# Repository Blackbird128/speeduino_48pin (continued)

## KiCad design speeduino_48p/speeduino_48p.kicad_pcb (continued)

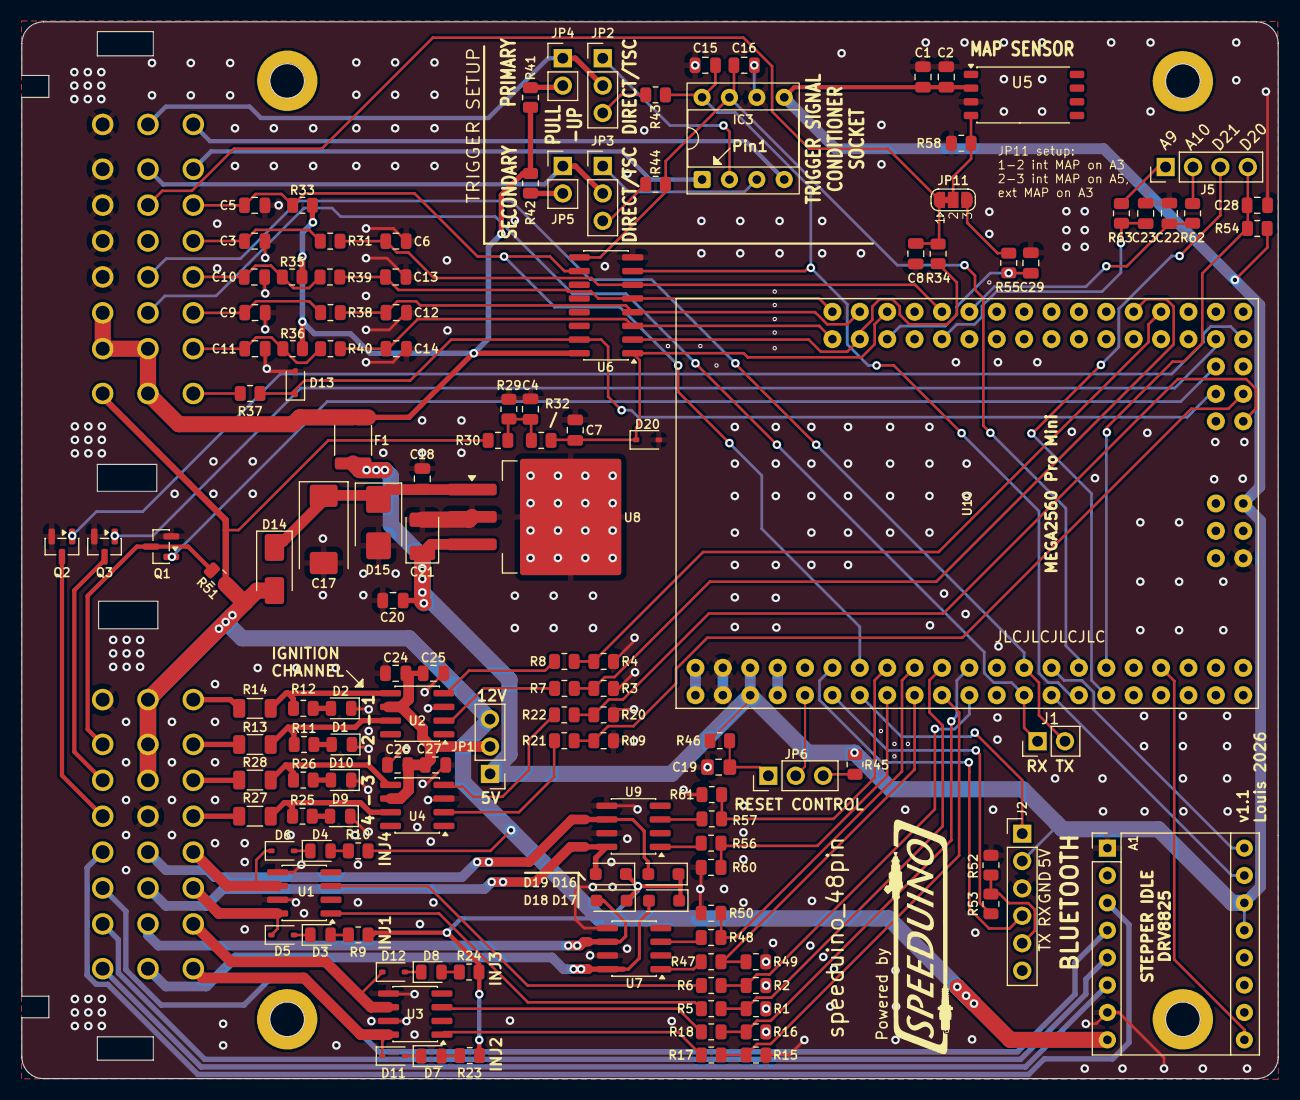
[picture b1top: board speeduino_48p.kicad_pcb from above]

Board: 2 copper layers, 116.5 x 98.0 mm, 143 parts (0 on the bottom side), 118 nets.

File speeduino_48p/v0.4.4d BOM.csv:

Reference; Quantity; Value; Footprint; Manufacturer_Name; Manufacturer_Part_Number; URL; Part #; Voltage; Allied_Number; Description; RS Part Number; RS Price/Stock; TR PN; Tube PN; Spice_Model; Spice_Netlist_Enabled; Spice_Primitive
C1 C15;2;0.01uF;Capacitor_SMD:C_0805_2012Metric;Yageo;CC0805KRX7R9BB103;https://www.digikey.com/product-detail/en/yageo/CC0805KRX7R9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;;;;;;;;;;;
C17;1;10uF;Capacitor_Tantalum_SMD:CP_EIA-7343-31_Kemet-D;Kemet;T491D106K050AT;https://www.digikey.com/product-detail/en/kemet/T491D106K050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;;35v;;;;;;;;;
C19;1;22uF;Capacitor_SMD:C_0805_2012Metric_Pad1.15x1.40mm_HandSolder;Samsung;CL21A226KQCLRNC;https://www.digikey.com.au/product-detail/en/samsung-electro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;;;;;;;;;;;
C21;1;47uF;Capacitor_Tantalum_SMD:CP_EIA-3528-21_Kemet-B;AVX;TAJB476K006RNJ;https://www.digikey.com/product-detail/en/avx-corporation/TA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;;10v;;;;;;;;;
C24 C26 C3 C9 C10 C11 C4 C16 C18 C20 C23 C22 C28;13;0.1uF;Capacitor_SMD:C_0805_2012Metric;Yageo;CC0805KRX7R9BB104;https://www.digikey.com.au/product-detail/en/yageo/CC0805KRX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;;;;;;;;;;;
C25 C27 C2;3;1uF;Capacitor_SMD:C_0805_2012Metric;Yageo;CC0805KKX7R7BB105;https://www.digikey.com/product-detail/en/yageo/CC0805KKX7R7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;;;;;;;;;;;
C6 C12 C13 C14 C7 C5;6;0.22uF;Capacitor_SMD:C_0805_2012Metric;Samsung;CL21B224KOCNNNC;https://www.digikey.com/product-detail/en/samsung-electro-me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;;;;;;;;;;;
C8 C29;2;470pf;Capacitor_SMD:C_0805_2012Metric;Yageo;CC0805KRX7R9BB471;https://www.digikey.com/product-detail/en/yageo/CC0805KRX7R9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;;;;;;;;;;;
D12 D11 D5 D6;4;D;Diode_SMD:D_SOD-323;MCC;1N4448WX-TP;https://www.digikey.com/product-detail/en/micro-commercial-c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;;;;;;;;;;;
D13 D20;2;D_Zener;Diode_SMD:D_SOD-323;On Semi;MM3Z5V1ST1G;https://www.digikey.com/product-detail/en/on-semiconductor/M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;MM3Z5V1ST1G;;;;;;;;;;
D14;1;B130-13-F;Diode_SMD:D_SMA;Diodes Inc;B130-13-F;https://www.digikey.com.au/product-detail/en/diodes-incorpor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;;;;;;;;;;;
D15;1;D_TVS;Diode_SMD:D_SMB;Bournes Inc.;SMBJ40A-Q;https://www.digikey.com.au/product-detail/en/bourns-inc/SMBJ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;;;;;;;;;;;
D19 D16 D17 D18;4;D;Diode_SMD:D_SOD-123F;ONSEMI;S110FA;https://www.digikey.com/en/products/detail/on-semiconductor/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;;;;;;;;;;;
D4 D3 D8 D7 D1 D2 D9 D10;8;LED;LED_SMD:LED_0805_2012Metric;Osram;LH R974-LP-1;https://www.digikey.com/product-detail/en/osram-opto-semicon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;;;;;;;;;;;
F1 F2;2;Polyfuse;Fuse:Fuse_1812_4532Metric;Bel Fuse;0ZCC0050FF2C;https://www.digikey.com.au/product-detail/en/bel-fuse-inc/0Z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;;;;;;;;;;;
IC3;2;Trig Cond Socket;Package_DIP:DIP-8_W7.62mm_Socket;Sullins Connector Solutions;PPTC041LFBN-RC;https://www.digikey.com.au/product-detail/en/sullins-connect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;;;;;;;;;;;
J3;1;Conn_01x02;TerminalBlock_Phoenix:TerminalBlock_Phoenix_PT-1,5-2-5.0-H_1x02_P5.00mm_Horizontal;TE;282836-2;https://www.digikey.com.au/product-detail/en/te-connectivity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;;;;;;;;;;;
J4;1;Conn_02x20_Counter_Clockwise;Connector_IDC:IDC-Header_2x20_P2.54mm_Vertical;CNC Tech;571-5103308-8;https://www.digikey.com.au/products/en?keywords=1175-1614-ND;;;;;;;;;;;
JP1;1;Ignition Voltage;Connector_PinHeader_2.54mm:PinHeader_1x03_P2.54mm_Vertical;Harwin Inc;M20-9990345;https://www.digikey.com.au/products/en?keywords=M20-9990345;;;;;;;;;;;
JP2 JP3;2;VR-HALL;Connector_PinHeader_2.54mm:PinHeader_1x03_P2.54mm_Vertical;Harwin Inc;M20-9990345;https://www.digikey.com.au/products/en?keywords=M20-9990345;;;;;;;;;;;
JP5 JP4;2;PULL-UP;Connector_PinHeader_2.54mm:PinHeader_1x02_P2.54mm_Vertical;Harwin Inc;M20-9990245;https://www.digikey.com.au/products/en?keywords=M20-9990245;;;;;;;;;;;
Q1 Q3 Q2;3;SSM3K357R;Package_TO_SOT_SMD:SOT-23;Toshiba;SSM3K357R;https://www.digikey.com.au/product-detail/en/toshiba-semicon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;;;;;;;;;;;
R1 R2 R15 R16 R3 R4 R19 R20 R50 R49 R61 R60;12;100k;Resistor_SMD:R_0805_2012Metric;Yageo;RC0805FR-07100KL;https://www.digikey.com/product-detail/en/yageo/RC0805FR-071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;;;;;;;;;;;
R10 R9 R24 R23 R11 R12 R25 R26 R33;9;2.4k;Resistor_SMD:R_0805_2012Metric;Yageo;RC0805FR-072K4L;https://www.digikey.com/product-detail/en/yageo/RC0805FR-072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;;;;;;;;;;;
R27 R28 R13 R14;4;10R;Resistor_SMD:R_1206_3216Metric;Yageo;RC1206FR-0710RL;https://www.digikey.com/en/products/detail/yageo/RC1206FR-07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;;;;;;;;;;;
R30;1;3.9k;Resistor_SMD:R_0805_2012Metric;Yageo;RC0805FR-073K9L;https://www.digikey.com/product-detail/en/yageo/RC0805FR-073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;;;;;;;;;;;
R34 R31 R38 R39 R40 R32 R55 R63 R62;9;470R;Resistor_SMD:R_0805_2012Metric;Panasonic;ERJ-6ENF4700V;https://www.digikey.com/product-detail/en/panasonic-electron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;;;;;;;;;;;
R35 R36;2;2.49k;Resistor_SMD:R_0805_2012Metric;Yageo;RT0805BRD072K49L;https://www.digikey.com/product-detail/en/yageo/RT0805BRD072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;;;;;;;;;;;
R43 R44;2;220R;Resistor_SMD:R_0805_2012Metric;Yageo;RC0805FR-07220RL;https://www.digikey.com/product-detail/en/yageo/RC0805FR-072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;;;;;;;;;;;
R45 R51;2;10k;Resistor_SMD:R_0805_2012Metric;Yageo;RC0805JR-0710KL;https://www.digikey.com/product-detail/en/yageo/RC0805JR-071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;;;;;;;;;;;
R46;1;120R;Resistor_SMD:R_0805_2012Metric;Yageo;RC0805FR-07120RL;https://www.digikey.com/product-detail/en/yageo/RC0805FR-071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;;;;;;;;;;;
R5 R6 R17 R18 R7 R8 R21 R22 R29 R37 R41 R42 R47 R48 R56 R57 R53 R54;18;1k;Resistor_SMD:R_0805_2012Metric;Yageo;RC0805FR-071KL;https://www.digikey.com/product-detail/en/yageo/RC0805FR-071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;;;;;;;;;;;
R52;1;2k;Resistor_SMD:R_0805_2012Metric;Yageo;RC0805FR-072KL;https://www.digikey.com/product-detail/en/yageo/RC0805FR-072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;;;;;;;;;;;
S1;1;AYZ0202AGRLC;Misc:AYZ0202AGRLC;C & K COMPONENTS;AYZ0202AGRLC;https://www.digikey.com.au/product-detail/en/c-k/AYZ0202AGRL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;;;70417470;AYZ0202AGRLC (Slide Switches);7931504P;http://uk.rs-online.com/web/p/products/7931504P;;;;;
U1 U3 U7 U9;4;VNLD5090;Package_SO:SOIC-8_3.9x4.9mm_P1.27mm;STMicro;VNLD5090-E;https://www.digikey.com.au/products/en?keywords=VNLD5090-E;;;;;;;;;;;
U2 U4;2;IXDN602;Package_SO:SOIC-8_3.9x4.9mm_P1.27mm;IXYS;IXDN602SIATR;https://www.digikey.com/en/products/detail/ixys-integrated-c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;;;;;;;;;;;
U5;1;MPX4250;Misc:MPX4250;NXP;MPX4250AP;https://www.digikey.com.au/product-detail/en/nxp-usa-inc/MPX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;;;;;;;;;;;
U6;1;SP720;Package_SO:SOIC-16_3.9x9.9mm_P1.27mm;Littelfuse;SP720ABTG;https://www.digikey.com/product-detail/en/littelfuse-inc/SP7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;;;;;;;;;;;
U8;1;LM2940S-5.0/NOPB;Package_TO_SOT_SMD:TO-263-3_TabPin2;TI;LM2940S-5.0/NOPB;https://www.digikey.com.au/products/en?keywords=LM2940S-5.0%2FNOPB;;;;;;;LM2940SX-5.0/NOPB;LM2940S-5.0/NOPB;;;

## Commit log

2026-01-11 Hardware
2026-01-11 README
    Updated readme
2026-01-11 Add image to README
    Added an image to the README
2026-02-25 v1.1
